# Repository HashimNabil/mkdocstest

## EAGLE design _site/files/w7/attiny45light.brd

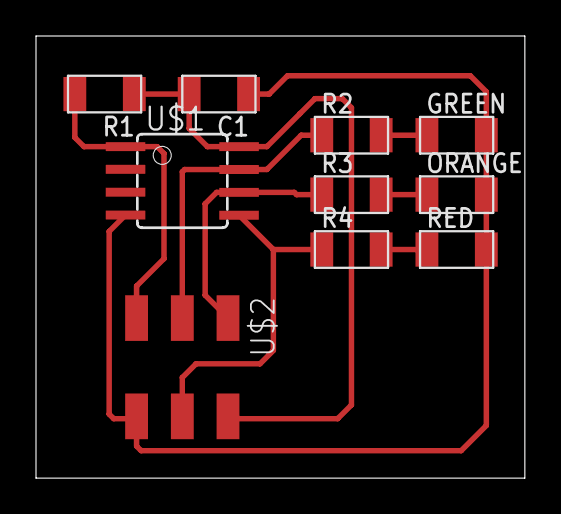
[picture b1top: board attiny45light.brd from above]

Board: 2 copper layers, 27.2 x 24.6 mm, 10 parts (0 on the bottom side), 9 nets.

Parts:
C1: 1uF; C1206FAB
GREEN: LEDFAB1206; LED1206FAB
ORANGE: LEDFAB1206; LED1206FAB
R1: 10K; R1206FAB
R2, R3, R4: 499; R1206FAB
RED: LEDFAB1206; LED1206FAB
U$1: UC_ATTINY45SI; SOIC8
U$2: CONN_03X2_AVRISPSMD; 2X03SMD

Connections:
GND: C1.1, GREEN.2, ORANGE.2, RED.2, U$1.4, U$2.6
MISO: R3.1, U$1.6, U$2.1
MOSI: R4.1, U$1.5, U$2.4
unnamed: GREEN.1, R2.2
unnamed: ORANGE.1, R3.2
unnamed: R4.2, RED.1
RST: R1.2, U$1.1, U$2.5
SCK: R2.1, U$1.7, U$2.3
VCC: C1.2, R1.1, U$1.8, U$2.2
